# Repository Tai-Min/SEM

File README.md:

# Simple Enclosure Manager
This little board allows you to control your 3d printer's enclosure using physical buttons or MQTT (using scripts, [Domoticz](https://www.domoticz.com/), [Home assistant](https://www.home-assistant.io/) or [Octoprint](https://octoprint.org/) events). The target software for this board is [Tasmota](https://tasmota.github.io/docs/).

## Features
* Powered by 12V power supply,
* Based on ESP-12E,
* Two 12V controllable outputs designed to control enclosure's LEDs and carbon filter fan , 1.5A total, supports PWM,
* One mains relay for printer's power supply, up to 10A at 230V,
* Three button inputs to control LEDs, carbon filter fan and printer's PSU directly
* 12V power connector secured for overvoltage, reverse voltage and by 2A ressetable fuse,
* Mains power connector secured for overvoltage and by 10A fast fuse.

## Assembly
### Get the board
The board is rather too hard to be etched (thin traces and small vias) so I would suggest using services of some PCB manufacturer to make it.<br/>

### Soldering
When you get the board and required components, start soldering smallest SMD components such as resistors and capacitors, then solder ESP-12 module and THT components. Finish the job by soldering connectors, buttons and relay.

## Uploading the firmware
For flashing the firmware you would need some USB to UART converter, or you can use NodeMCU to act as one.
#### WARNING This board uses 3.3V voltage level so make sure that choosen USB to UART converter also uses 3.3V as higher voltages such as 5V will fry the board and let the magic smoke out.

#### WARNING Before flashing the firmware make sure that the board is not connected to any other power source such as 12V

Also, you need to remove "GPIO 3" jumper before proceeding further.

### Using the converter
Simply connect the converter to the board:
* VCC <-> 3.3V
* Gnd <-> Gnd
* Rx <-> Tx
* Tx <-> Rx

Then put your device into programming mode by holding "FLASH" button and then pressing "RESET" button. After a while release the "FLASH" button. Now the device is in flash mode.

Now, all you need to do is to flash Tasmota firmware into your board. Easiest method to do this is to use [Tasmotizer](https://tasmota.github.io/docs/Getting-Started/#flashing).
### Using NodeMCU
Short EN pin to GND and simply connect it to the board:
* 3.3V <-> 3.3V
* Gnd <-> Gnd
* Tx <-> Tx
* Rx <-> Rx

Then put your device into programming mode by holding "FLASH" button and then pressing "RESET" button. After a while release the "FLASH" button. Now the device is in flash mode.

Now, all you need to do is to flash Tasmota firmware into your board. Easiest method to do this is to use [Tasmotizer](https://tasmota.github.io/docs/Getting-Started/#flashing).

## Examples
All of the examples listed here require a priori knowledge about used programs.
### Simple mosquitto script
<TODO>

### Octoprint events
<TODO>

### Hassio integration
<TODO>

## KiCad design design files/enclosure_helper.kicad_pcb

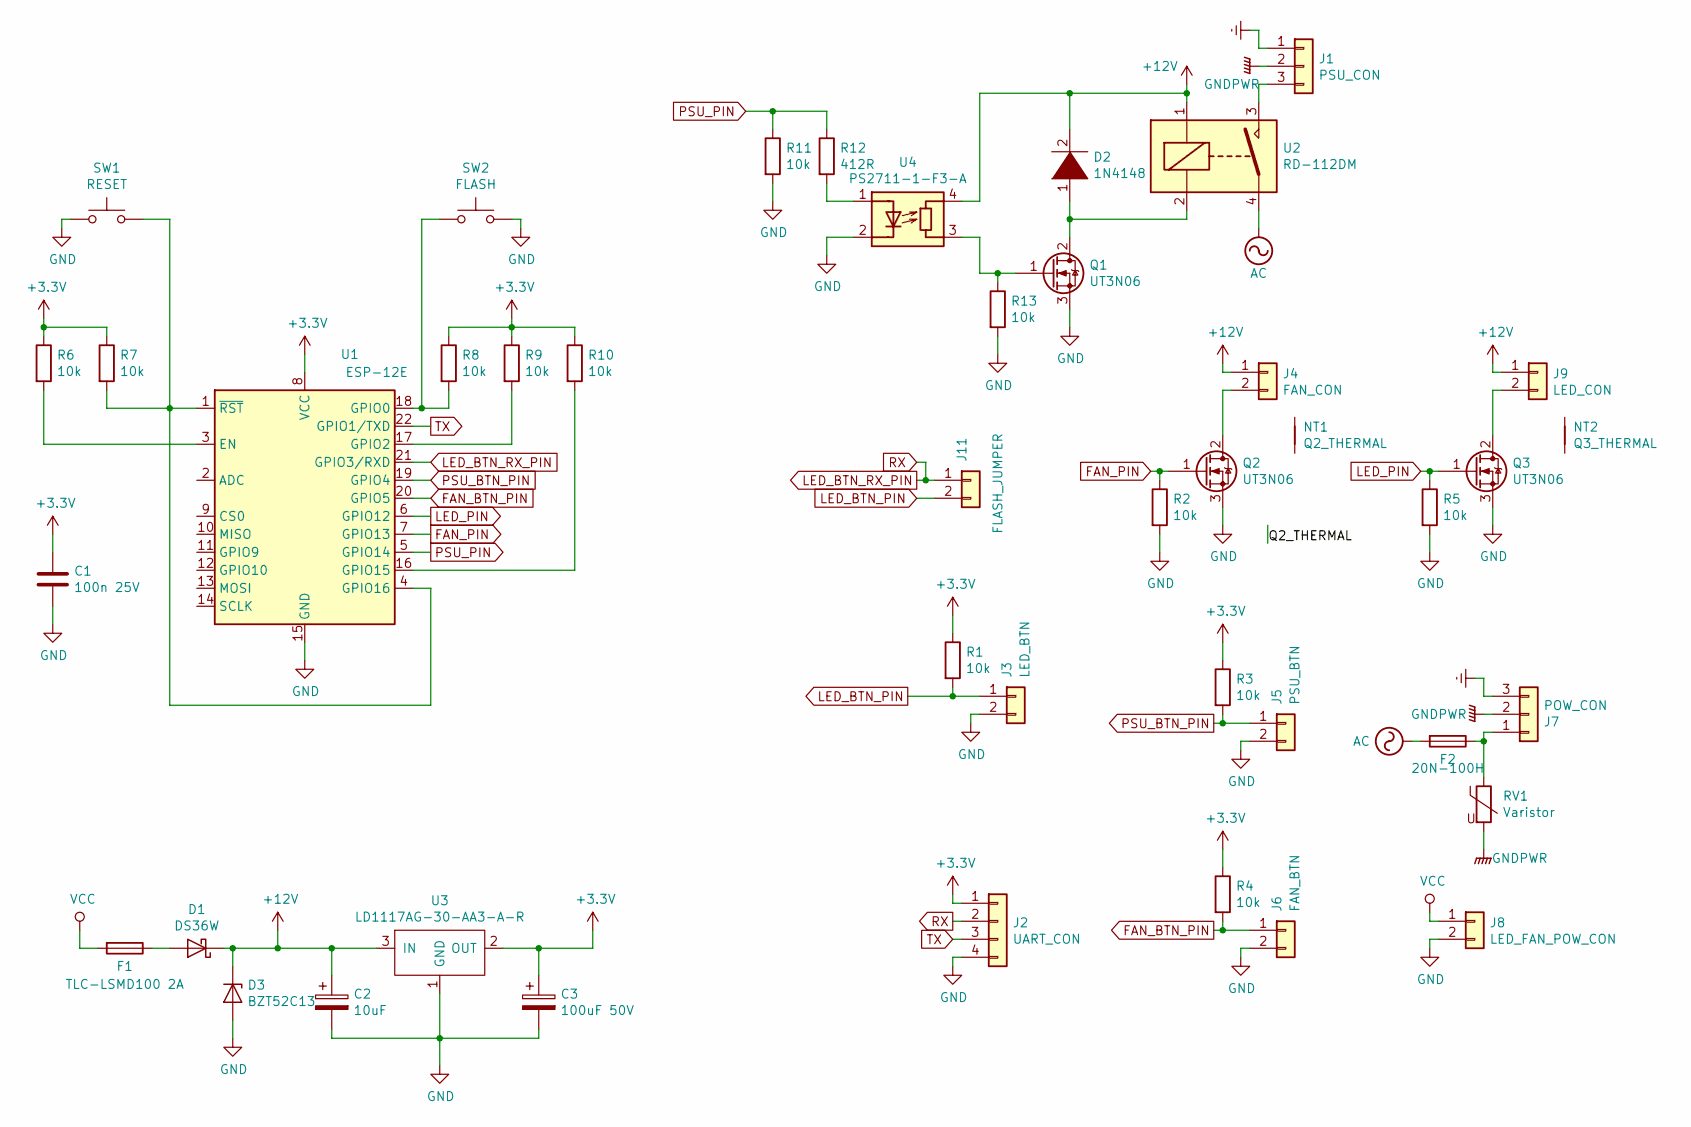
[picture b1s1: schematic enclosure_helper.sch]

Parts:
C1: 100n 25V; C_1206_3216Metric_Pad1.42x1.75mm_HandSolder
C2: 10uF; CP_Elec_6.3x5.4
C3: 100uF 50V; CP_Elec_8x10.5
D1: DS36W; D_SOD-123
D2: 1N4148; D_DO-35_SOD27_P7.62mm_Horizontal
D3: BZT52C13; D_SOD-123
F1: TLC-LSMD100 2A; Fuse_2920_7451Metric_Pad2.10x5.45mm_HandSolder
F2: 20N-100H; R_Axial_DIN0411_L9.9mm_D3.6mm_P5.08mm_Vertical
J1: PSU_CON; PhoenixContact_MSTBA_2,5_3-G-5,08_1x03_P5.08mm_Horizontal
J2: UART_CON; PinHeader_1x04_P2.54mm_Vertical
J3: LED_BTN; BarrelJack_Wuerth_6941xx301002
J4: FAN_CON; BarrelJack_Wuerth_6941xx301002
J5: PSU_BTN; BarrelJack_Wuerth_6941xx301002
J6: FAN_BTN; BarrelJack_Wuerth_6941xx301002
J7: POW_CON; PhoenixContact_MSTBA_2,5_3-G-5,08_1x03_P5.08mm_Horizontal
J8: LED_FAN_POW_CON; PhoenixContact_MSTBA_2,5_2-G_1x02_P5.00mm_Horizontal
J9: LED_CON; BarrelJack_Wuerth_6941xx301002
J11: FLASH_JUMPER; PinHeader_1x02_P2.54mm_Vertical
NT1: Q2_THERMAL; NetTie-2_SMD_Pad0.5mm
NT2: Q3_THERMAL; NetTie-2_SMD_Pad0.5mm
Q1: UT3N06; SOT-89-3_Handsoldering
Q2, Q3: UT3N06; TO-251-3-1EP_Horizontal_TabDown
R1, R2, R3, R4, R5, R6, R7, R8, R9, R10, R11, R13: 10k; R_1206_3216Metric_Pad1.42x1.75mm_HandSolder
R12: 412R; R_1206_3216Metric_Pad1.42x1.75mm_HandSolder
RV1: Varistor; RV_Disc_D12mm_W6.7mm_P7.5mm
SW1: RESET; SW_PUSH_6mm
SW2: FLASH; SW_PUSH_6mm
U1: ESP-12E
U2: RD-112DM; RD_112DM
U3: LD1117AG-30-AA3-A-R; SOT-223
U4: PS2711-1-F3-A; SOP-4_3.8x4.1mm_P2.54mm

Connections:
+3V3: C1.1, C3.1, J2.1, R1.1, R3.1, R4.1, R6.1, R7.1, R8.1, R9.1, R10.1, U1.8 (VCC), U3.2 (OUT)
+12V: C2.1, D1.1 (K), D2.2 (A), D3.1 (K), J4.1, J9.1, U2.1, U3.3 (IN), U4.4 (R)
AC: F2.2, U2.4
Earth: J1.1, J7.3
FAN_BTN_PIN: J6.1, R4.2, U1.20 (GPIO5)
FAN_PIN: Q2.1 (G), R2.1, U1.7 (GPIO13)
GND: C1.2, C2.2, C3.2, D3.2 (A), J2.4, J3.2, J5.2, J6.2, J8.2, Q1.3 (S), Q2.3 (S), Q3.3 (S), R2.2, R5.2, R11.2, R13.2, SW1.1, SW2.2, U1.15 (GND), U3.1 (GND), U4.2 (K)
GNDPWR: J1.2, J7.2, RV1.2
LED_BTN_PIN: J3.1, J11.2, R1.2
LED_BTN_RX_PIN: J2.2, J11.1, U1.21 (GPIO3/RXD)
LED_PIN: Q3.1 (G), R5.1, U1.6 (GPIO12)
unnamed: D1.2 (A), F1.1
unnamed: D2.1 (K), Q1.2 (D), U2.2
unnamed: F2.1, J7.1, RV1.1
unnamed: J1.3, U2.3
unnamed: J4.2, Q2.2 (D)
unnamed: J9.2, Q3.2 (D)
unnamed: NT1.1, Q3.4
unnamed: NT2.1, Q2.4
unnamed: Q1.1 (G), R13.1, U4.3 (R)
unnamed: R6.2, U1.3 (EN)
unnamed: R7.2, SW1.2, U1.1 (~RST), U1.4 (GPIO16)
unnamed: R8.2, SW2.1, U1.18 (GPIO0)
unnamed: R9.2, U1.17 (GPIO2)
unnamed: R10.2, U1.16 (GPIO15)
unnamed: R12.2, U4.1 (A)
PSU_BTN_PIN: J5.1, R3.2, U1.19 (GPIO4)
PSU_PIN: R11.1, R12.1, U1.5 (GPIO14)
TX: J2.3, U1.22 (GPIO1/TXD)
VCC: F1.2, J8.1

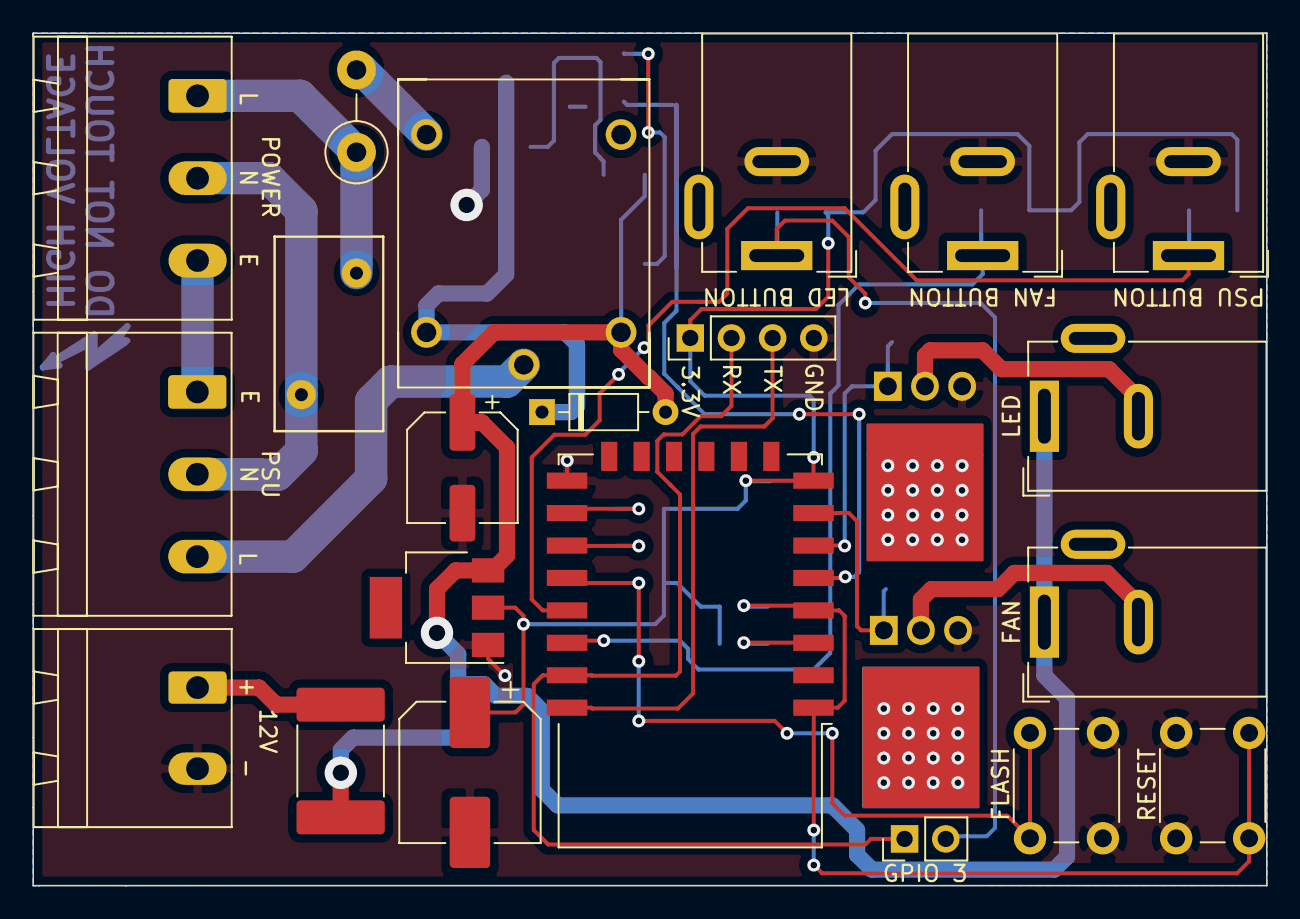
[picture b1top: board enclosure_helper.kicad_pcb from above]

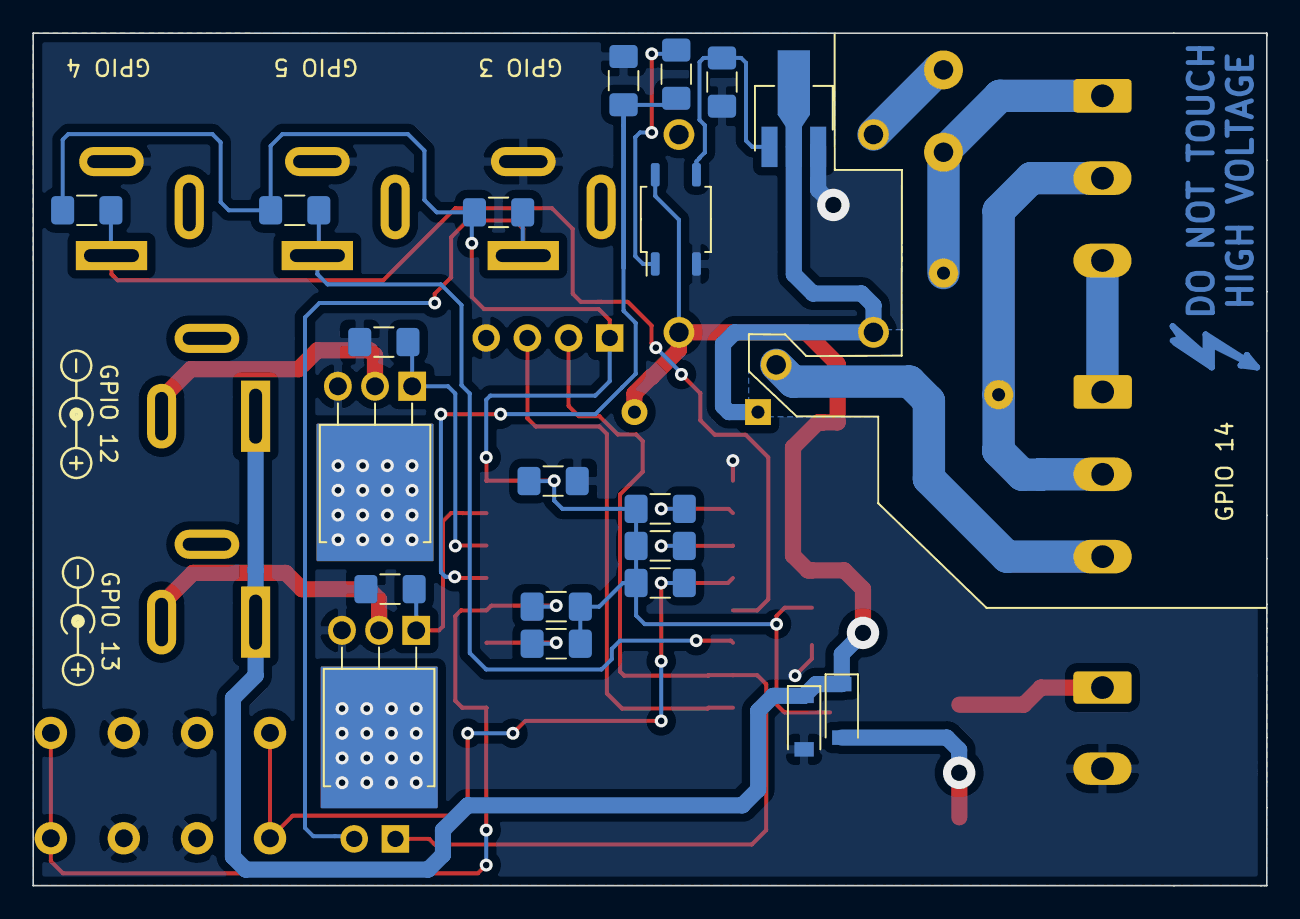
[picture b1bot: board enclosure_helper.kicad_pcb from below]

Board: 2 copper layers, 76.1 x 52.6 mm, 43 parts (20 on the bottom side), 30 nets.

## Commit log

2020-09-08 Create LICENSE
2020-09-10 Add varistor for mains, add high voltage warning
